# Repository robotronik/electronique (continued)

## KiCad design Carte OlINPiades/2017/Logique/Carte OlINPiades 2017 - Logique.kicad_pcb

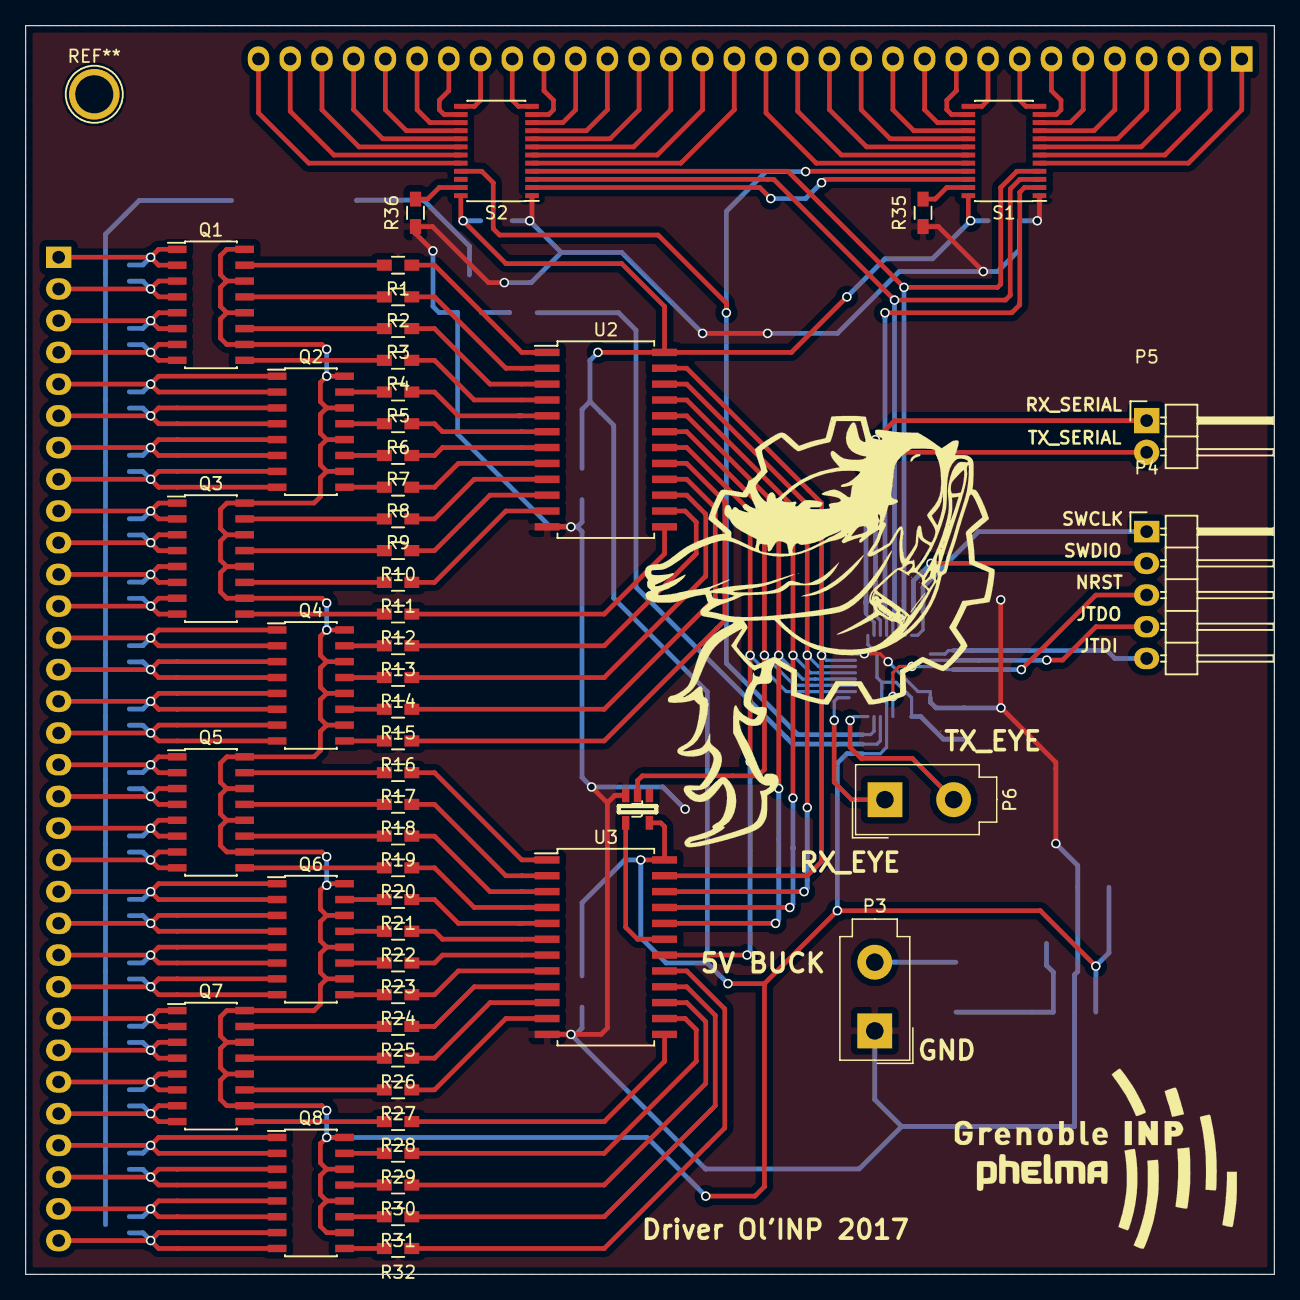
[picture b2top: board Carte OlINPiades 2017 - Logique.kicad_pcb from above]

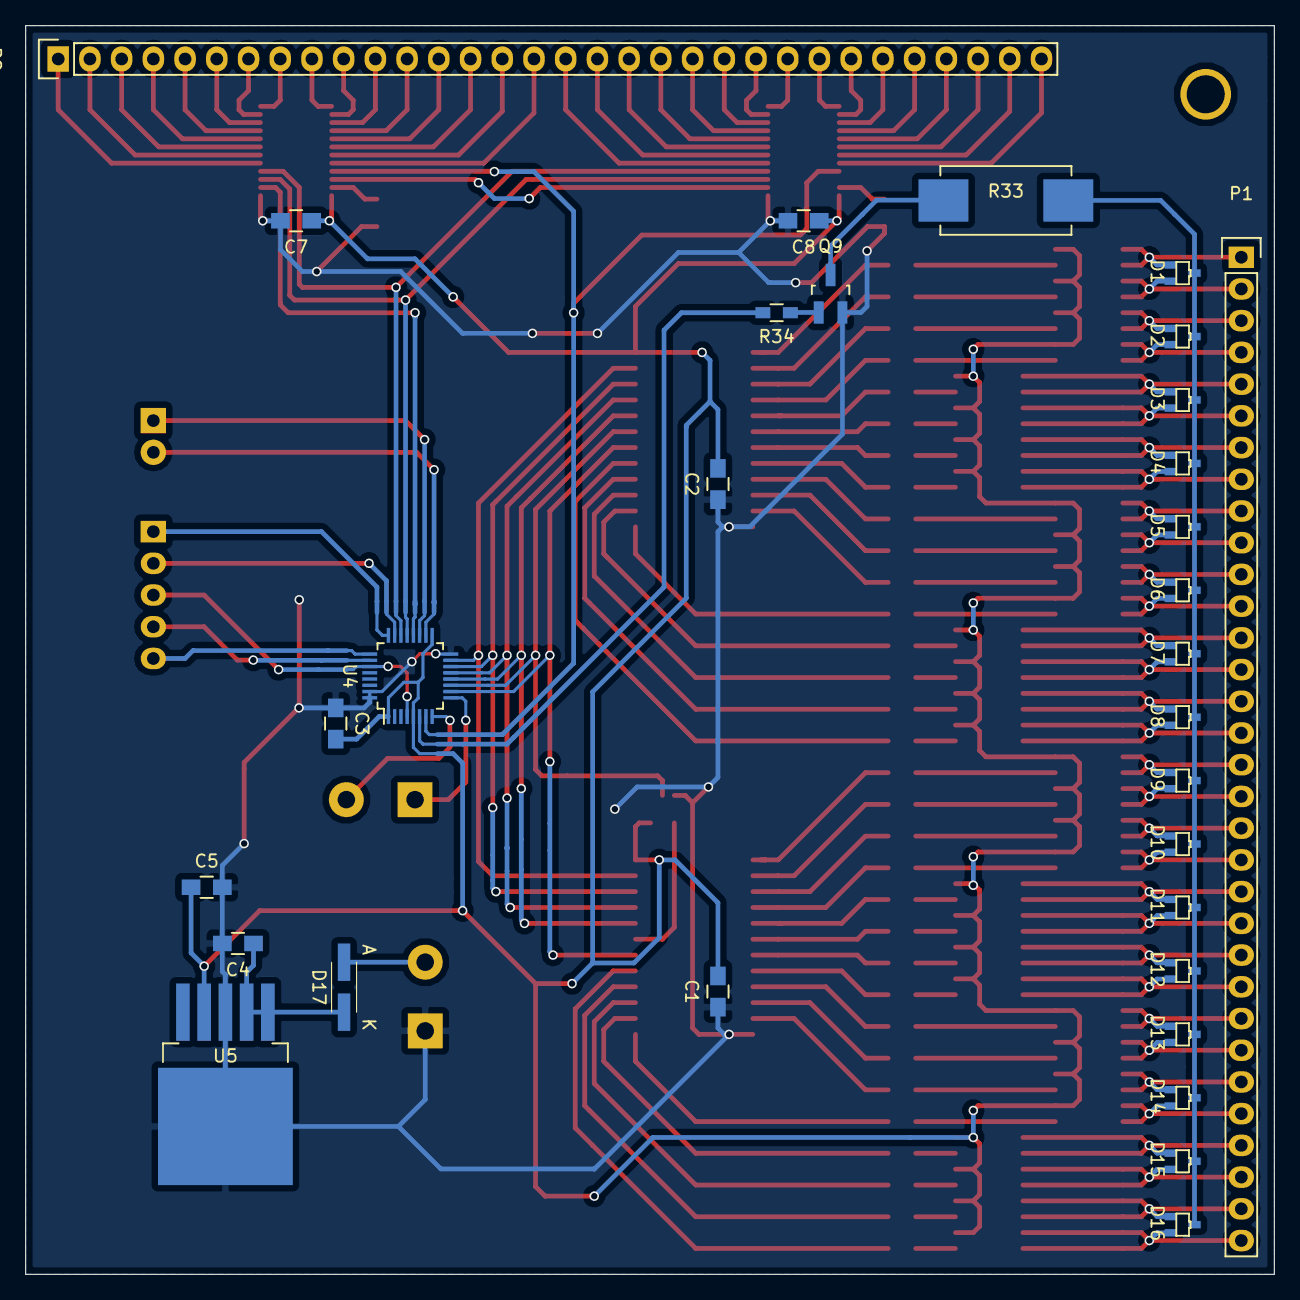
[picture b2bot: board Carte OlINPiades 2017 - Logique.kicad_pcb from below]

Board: 2 copper layers, 100.0 x 100.0 mm, 82 parts (31 on the bottom side), 159 nets.

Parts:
C1, C2: 100n; C_0805_HandSoldering
C3, C7, C8: 100nF; C_0805_HandSoldering
C4: 1µF; C_0805_HandSoldering
C5: 47µF; C_0805_HandSoldering
D1, D2, D3, D4, D5, D6, D7, D8, D9, D10, D11, D12, D13, D14, D15, D16: BAT54CW; SOT-323
D17: RFN2L4STE25; SMA_Handsoldering
P1, P2: CONN_01X32; Pin_Header_Straight_1x32
P3, P6: CONN_01X02; Molex_MiniFit-JR-5556-02A_2x01x4.20mm_Straight
P4: CONN_01X05; Pin_Header_Angled_1x05
P5: CONN_01X02; Pin_Header_Angled_1x02
Q1, Q2, Q3, Q4, Q5, Q6, Q7, Q8: MMPQ2907A; SOIC-16_3.9x9.9mm_Pitch1.27mm
Q9: DSS4160T; SOT-23_Handsoldering
R1, R2, R3, R4, R5, R6, R7, R8, R9, R10, R11, R12, R13, R14, R15, R16, R17, R18, R19, R20, R21, R22, R23, R24, R25, R26, R27, R28, R29, R30, R31, R32: 470; R_0603_HandSoldering
R33: 8.2; SM_3
R34: 1.7k; R_0603_HandSoldering
R35, R36: 4k; R_0603_HandSoldering
S1, S2: CAT4016; TSSOP-24_4.4x7.8mm_Pitch0.65mm
U1: 74AHC1G; SOT-23-5
U2, U3: CD74HC154; SOIC-24_7.5x15.4mm_Pitch1.27mm
U4: STM32F303K8; LQFP-32_5x5mm_Pitch0.5mm
U5: NCP59301DSS33R4G; TO-263-5Lead

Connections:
+3V3: C1.2, C2.2, C3.2, C5.1, C7.1, C8.1, Q1.10, Q1.12, Q1.14, Q1.16, Q2.10, Q2.12, Q2.14, Q2.16, Q3.10, Q3.12, Q3.14, Q3.16, Q4.10, Q4.12, Q4.14, Q4.16, Q5.10, Q5.12, Q5.14, Q5.16, Q6.10, Q6.12, Q6.14, Q6.16, Q7.10, Q7.12, Q7.14, Q7.16, Q8.10, Q8.12, Q8.14, Q8.16, S1.24, S2.24, U1.5, U2.24, U3.24, U4.1, U4.5, U4.17, U5.4
+5V: C4.1, D17.1, U5.1, U5.2
BLANK: S1.21, S2.21, U4.7
CLK_COL: S1.3, S2.3, U4.21
DATA: U2.18, U3.18, U4.10
GND: C1.1, C2.1, C3.1, C4.2, C5.2, C7.2, C8.2, P3.1, Q9.2, R35.1, R36.1, S1.1, S2.1, U1.3, U2.12, U3.12, U4.16, U4.31, U4.32, U5.3
JTDI: P4.5, U4.25
JTDO: P4.4, U4.26
LATCH_COL: S1.4, S2.4, U4.22
LINE_0: U2.23, U3.23, U4.15
LINE_1: U2.22, U3.22, U4.14
LINE_2: U2.21, U3.21, U4.13
LINE_3: U2.20, U3.20, U4.12
LINE_4: U1.2, U2.19, U4.11
NRST: P4.3, U4.4, U4.27
unnamed: D1.1, P1.1, Q1.1, Q1.2
unnamed: D1.2, P1.2, Q1.3, Q1.4
unnamed: D1.3, D2.3, D3.3, D4.3, D5.3, D6.3, D7.3, D8.3, D9.3, D10.3, D11.3, D12.3, D13.3, D14.3, D15.3, D16.3, R33.1
unnamed: D2.1, P1.3, Q1.5, Q1.6
unnamed: D2.2, P1.4, Q1.7, Q1.8
unnamed: D3.1, P1.5, Q2.1, Q2.2
unnamed: D3.2, P1.6, Q2.3, Q2.4
unnamed: D4.1, P1.7, Q2.5, Q2.6
unnamed: D4.2, P1.8, Q2.7, Q2.8
unnamed: D5.1, P1.9, Q3.1, Q3.2
unnamed: D5.2, P1.10, Q3.3, Q3.4
unnamed: D6.1, P1.11, Q3.5, Q3.6
unnamed: D6.2, P1.12, Q3.7, Q3.8
unnamed: D7.1, P1.13, Q4.1, Q4.2
unnamed: D7.2, P1.14, Q4.3, Q4.4
unnamed: D8.1, P1.15, Q4.5, Q4.6
unnamed: D8.2, P1.16, Q4.7, Q4.8
unnamed: D9.1, P1.17, Q5.1, Q5.2
unnamed: D9.2, P1.18, Q5.3, Q5.4
unnamed: D10.1, P1.19, Q5.5, Q5.6
unnamed: D10.2, P1.20, Q5.7, Q5.8
unnamed: D11.1, P1.21, Q6.1, Q6.2
unnamed: D11.2, P1.22, Q6.3, Q6.4
unnamed: D12.1, P1.23, Q6.5, Q6.6
unnamed: D12.2, P1.24, Q6.7, Q6.8
unnamed: D13.1, P1.25, Q7.1, Q7.2
unnamed: D13.2, P1.26, Q7.3, Q7.4
unnamed: D14.1, P1.27, Q7.5, Q7.6
unnamed: D14.2, P1.28, Q7.7, Q7.8
unnamed: D15.1, P1.29, Q8.1, Q8.2
unnamed: D15.2, P1.30, Q8.3, Q8.4
unnamed: D16.1, P1.31, Q8.5, Q8.6
unnamed: D16.2, P1.32, Q8.7, Q8.8
unnamed: D17.2, P3.2
unnamed: P2.1, S1.5
unnamed: P2.2, S1.6
unnamed: P2.3, S1.7
unnamed: P2.4, S1.8
unnamed: P2.5, S1.9
unnamed: P2.6, S1.10
unnamed: P2.7, S1.11
unnamed: P2.8, S1.12
unnamed: P2.9, S1.13
unnamed: P2.10, S1.14
unnamed: P2.11, S1.15
unnamed: P2.12, S1.16
unnamed: P2.13, S1.17
unnamed: P2.14, S1.18
unnamed: P2.15, S1.19
unnamed: P2.16, S1.20
unnamed: P2.17, S2.5
unnamed: P2.18, S2.6
unnamed: P2.19, S2.7
unnamed: P2.20, S2.8
unnamed: P2.21, S2.9
unnamed: P2.22, S2.10
unnamed: P2.23, S2.11
unnamed: P2.24, S2.12
unnamed: P2.25, S2.13
unnamed: P2.26, S2.14
unnamed: P2.27, S2.15
unnamed: P2.28, S2.16
unnamed: P2.29, S2.17
unnamed: P2.30, S2.18
unnamed: P2.31, S2.19
unnamed: P2.32, S2.20
unnamed: Q1.9, R4.2
unnamed: Q1.11, R3.2
unnamed: Q1.13, R2.2
unnamed: Q1.15, R1.2
unnamed: Q2.9, R8.2
unnamed: Q2.11, R7.2
unnamed: Q2.13, R6.2
unnamed: Q2.15, R5.2
unnamed: Q3.9, R12.2
unnamed: Q3.11, R11.2
unnamed: Q3.13, R10.2
unnamed: Q3.15, R9.2
unnamed: Q4.9, R16.2
unnamed: Q4.11, R15.2
unnamed: Q4.13, R14.2
unnamed: Q4.15, R13.2
unnamed: Q5.9, R20.2
unnamed: Q5.11, R19.2
unnamed: Q5.13, R18.2
unnamed: Q5.15, R17.2
unnamed: Q6.9, R24.2
unnamed: Q6.11, R23.2
unnamed: Q6.13, R22.2
unnamed: Q6.15, R21.2
unnamed: Q7.9, R28.2
unnamed: Q7.11, R27.2
unnamed: Q7.13, R26.2
unnamed: Q7.15, R25.2
unnamed: Q8.9, R32.2
unnamed: Q8.11, R31.2
unnamed: Q8.13, R30.2
unnamed: Q8.15, R29.2
unnamed: Q9.1, R34.1
unnamed: Q9.3, R33.2
unnamed: R1.1, U2.1
unnamed: R2.1, U2.2
unnamed: R3.1, U2.3
unnamed: R4.1, U2.4
unnamed: R5.1, U2.5
unnamed: R6.1, U2.6
unnamed: R7.1, U2.7
unnamed: R8.1, U2.8
unnamed: R9.1, U2.9
unnamed: R10.1, U2.10
unnamed: R11.1, U2.11
unnamed: R12.1, U2.13
unnamed: R13.1, U2.14
unnamed: R14.1, U2.15
unnamed: R15.1, U2.16
unnamed: R16.1, U2.17
unnamed: R17.1, U3.1
unnamed: R18.1, U3.2
unnamed: R19.1, U3.3
unnamed: R20.1, U3.4
unnamed: R21.1, U3.5
unnamed: R22.1, U3.6
unnamed: R23.1, U3.7
unnamed: R24.1, U3.8
unnamed: R25.1, U3.9
unnamed: R26.1, U3.10
unnamed: R27.1, U3.11
unnamed: R28.1, U3.13
unnamed: R29.1, U3.14
unnamed: R30.1, U3.15
unnamed: R31.1, U3.16
unnamed: R32.1, U3.17
unnamed: R35.2, S1.23
unnamed: R36.2, S2.23
unnamed: S1.22, S2.2
unnamed: U1.4, U3.19
PURGE: R34.2, U4.6
RX_EYE: P6.1, U4.9
RX_SERIAL: P5.1, U4.19
SERIAL_IN: S1.2, U4.20
SWCLK: P4.1, U4.24
SWDIO: P4.2, U4.23
TX_EYE: P6.2, U4.8
TX_SERIAL: P5.2, U4.18

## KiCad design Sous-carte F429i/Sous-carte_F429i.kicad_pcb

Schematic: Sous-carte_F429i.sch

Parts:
D1, D2, D4, D5, D6, D7, D8, D10, D11, D12, D13, D14, D15, D16, D17, D18, D19: LED; LED_0805
D3, D9: D; Diode_DO-35_SOD27_Horizontal_RM10
P1, P2, P4, P5, P6, P7, P8, P12, P15, P16, P17: CONN_01X02; Molex_KK_6410-02
P3, P11: CONN_01X02; bornier2
P9, P13, P14: CONN_01X03; Molex_KK_6410-03
P10, P18, P19, P20, P21, P22, P23, P24, P25, P26, P27, P28, P30, P31, P32, P33, P34, P35, P36, P37, P38, P39, P40, P41, P42, P43, P44, P45, P46, P47, P48, P49, P50, P51, P52, P53, P54, P55, P56, P57, P58, P59, P60, P61, P62, P63, P64, P65, P66, P67, P68, P69, P70, P71, P72, P73, P74, P75, P76, P77, P78, P79, P80, P81, P82, P83, P84, P85, P86, P87, P88, P89, P91, P92, P93, P94, P95, P96, P97, P98, P99, P100, P101, P102, P103, P104, P105, P106, P107, P108, P109, P110, P111, P112, P113, P114, P115, P116, P117: CONN_01X01; Pin_Header_Straight_1x01
R1, R2, R3, R4, R5, R6, R7, R8, R9, R10, R11, R12, R13, R14, R15, R16, R17, R18, R19, R20, R21: R; R_0603_HandSoldering
stm1: STM32F429i-Discovery; stm32f429i-disco

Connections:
+5V: D3.1, D4.2 (A), P4.1, P13.1, P13.2, P13.3, stm1.1, stm1.2
+BATT: D9.1, D10.2 (A), P14.2
EQUIPE: stm1.33; also elsewhere on the board
GND: P3.1, P11.1, P14.1, R1.1, R2.1, R3.1, R4.1, R5.1, R6.1, R7.1, R8.1, R9.2, R10.2, R11.1, R12.2, R13.1, R14.1, R15.1, R16.1, R17.1, R18.2, R19.2, R20.2, R21.2, stm1.63, stm1.64, stm1.75, stm1.93, stm1.127, stm1.128; also elsewhere on the board
LED_1: D16.2 (A), stm1.16
LED_2: D17.2 (A), stm1.13
LED_3: D18.2 (A), stm1.14
LED_4: D19.2 (A), stm1.11
unnamed: D1.1 (K), R1.2
unnamed: D2.1 (K), R2.2
unnamed: D3.2, P3.2
unnamed: D4.1 (K), R6.2
unnamed: D5.1 (K), R3.2
unnamed: D6.1 (K), R4.2
unnamed: D7.1 (K), R7.2
unnamed: D8.1 (K), R8.2
unnamed: D9.2, P11.2
unnamed: D10.1 (K), R13.2
unnamed: D11.1 (K), R11.2
unnamed: D12.1 (K), R14.2
unnamed: D13.1 (K), R15.2
unnamed: D14.1 (K), R16.2
unnamed: D15.1 (K), R17.2
unnamed: D16.1 (K), R18.1
unnamed: D17.1 (K), R19.1
unnamed: D18.1 (K), R20.1
unnamed: D19.1 (K), R21.1
unnamed: P18.1, stm1.3
unnamed: P19.1, stm1.5
unnamed: P20.1, stm1.7
unnamed: P21.1, stm1.9
unnamed: P22.1, stm1.19
unnamed: P23.1, stm1.21
unnamed: P24.1, stm1.23
unnamed: P25.1, stm1.25
unnamed: P26.1, stm1.27
unnamed: P27.1, stm1.29
unnamed: P28.1, stm1.31
unnamed: P30.1, stm1.35
unnamed: P31.1, stm1.39
unnamed: P32.1, stm1.41
unnamed: P33.1, stm1.47
unnamed: P34.1, stm1.49
unnamed: P35.1, stm1.53
unnamed: P36.1, stm1.57
unnamed: P37.1, stm1.59
unnamed: P38.1, stm1.61
unnamed: P39.1, stm1.4
unnamed: P40.1, stm1.6
unnamed: P41.1, stm1.8
unnamed: P42.1, stm1.10
unnamed: P43.1, stm1.12
unnamed: P44.1, stm1.20
unnamed: P45.1, stm1.22
unnamed: P46.1, stm1.24
unnamed: P47.1, stm1.26
unnamed: P48.1, stm1.28
unnamed: P49.1, stm1.30
unnamed: P50.1, stm1.32
unnamed: P51.1, stm1.34
unnamed: P52.1, stm1.36
unnamed: P53.1, stm1.38
unnamed: P54.1, stm1.42
unnamed: P55.1, stm1.46
unnamed: P56.1, stm1.48
unnamed: P57.1, stm1.50
unnamed: P58.1, stm1.54
unnamed: P59.1, stm1.56
unnamed: P60.1, stm1.58
unnamed: P61.1, stm1.60
unnamed: P62.1, stm1.62
unnamed: P63.1, stm1.65, stm1.66
unnamed: P64.1, stm1.69
unnamed: P65.1, stm1.71
unnamed: P66.1, stm1.73
unnamed: P67.1, stm1.77
unnamed: P68.1, stm1.79
unnamed: P69.1, stm1.81
unnamed: P70.1, stm1.83
unnamed: P71.1, stm1.85
unnamed: P72.1, stm1.87
unnamed: P73.1, stm1.89
unnamed: P74.1, stm1.91
unnamed: P75.1, stm1.95
unnamed: P76.1, stm1.97
unnamed: P77.1, stm1.99
unnamed: P78.1, stm1.101
unnamed: P79.1, stm1.103
unnamed: P80.1, stm1.105
unnamed: P81.1, stm1.107
unnamed: P82.1, stm1.109
unnamed: P83.1, stm1.111
unnamed: P84.1, stm1.113
unnamed: P85.1, stm1.115
unnamed: P86.1, stm1.117
unnamed: P87.1, stm1.119
unnamed: P88.1, stm1.121
unnamed: P89.1, stm1.123
unnamed: P91.1, stm1.72
unnamed: P92.1, stm1.74
unnamed: P93.1, stm1.76
unnamed: P94.1, stm1.78
unnamed: P95.1, stm1.80
unnamed: P96.1, stm1.82
unnamed: P97.1, stm1.84
unnamed: P98.1, stm1.86
unnamed: P99.1, stm1.88
unnamed: P100.1, stm1.90
unnamed: P101.1, stm1.92
unnamed: P102.1, stm1.94
unnamed: P103.1, stm1.96
unnamed: P104.1, stm1.98
unnamed: P105.1, stm1.100
unnamed: P106.1, stm1.102
unnamed: P107.1, stm1.104
unnamed: P108.1, stm1.106
unnamed: P109.1, stm1.108
unnamed: P110.1, stm1.110
unnamed: P111.1, stm1.112
unnamed: P112.1, stm1.114
unnamed: P113.1, stm1.116
unnamed: P114.1, stm1.118
unnamed: P115.1, stm1.120
unnamed: P116.1, stm1.122
unnamed: P117.1, stm1.124
START: P4.2, R5.2, stm1.15
SWITCH_0: P9.1, R9.1, stm1.55
SWITCH_1: P9.2, R10.1, stm1.126
SWITCH_2: P9.3, R12.1, stm1.125
UART4_RX: D2.2 (A), P2.2, P6.2, stm1.44
UART4_TX: D6.2 (A), P2.1, P6.1, stm1.45
UART5_RX: D7.2 (A), P7.2, P8.2, stm1.40
UART5_TX: D8.2 (A), P7.1, P8.1, stm1.43
UART7_RX: D12.2 (A), P12.2, P15.2, stm1.67
UART7_TX: D13.2 (A), P12.1, P15.1, stm1.70
UART8_RX: D14.2 (A), P16.2, P17.2, stm1.17
UART8_TX: D15.2 (A), P16.1, P17.1, stm1.18
USART1_RX: D1.2 (A), P1.2, P5.2, stm1.51
USART1_TX: D5.2 (A), P1.1, P5.1, stm1.52
USART2_TX: D11.2 (A), P10.1, P14.3, stm1.37

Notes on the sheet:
UART CAPTEURS US
Devant/Droite
Devant/Gauche
Arrière/Droite
Arrière/Gauche
UART ASSER
UART XL320 Half-Duplex
ALIMENTATIONS
7.5V
DIGITAL INPUTS
Tirette
DIGITAL OUTPUTS
Led debug 1
Led debug 2
Led debug 3
Led debug 4
STM32F429I-DISCOVERY
Configuration coquillages
Equipe

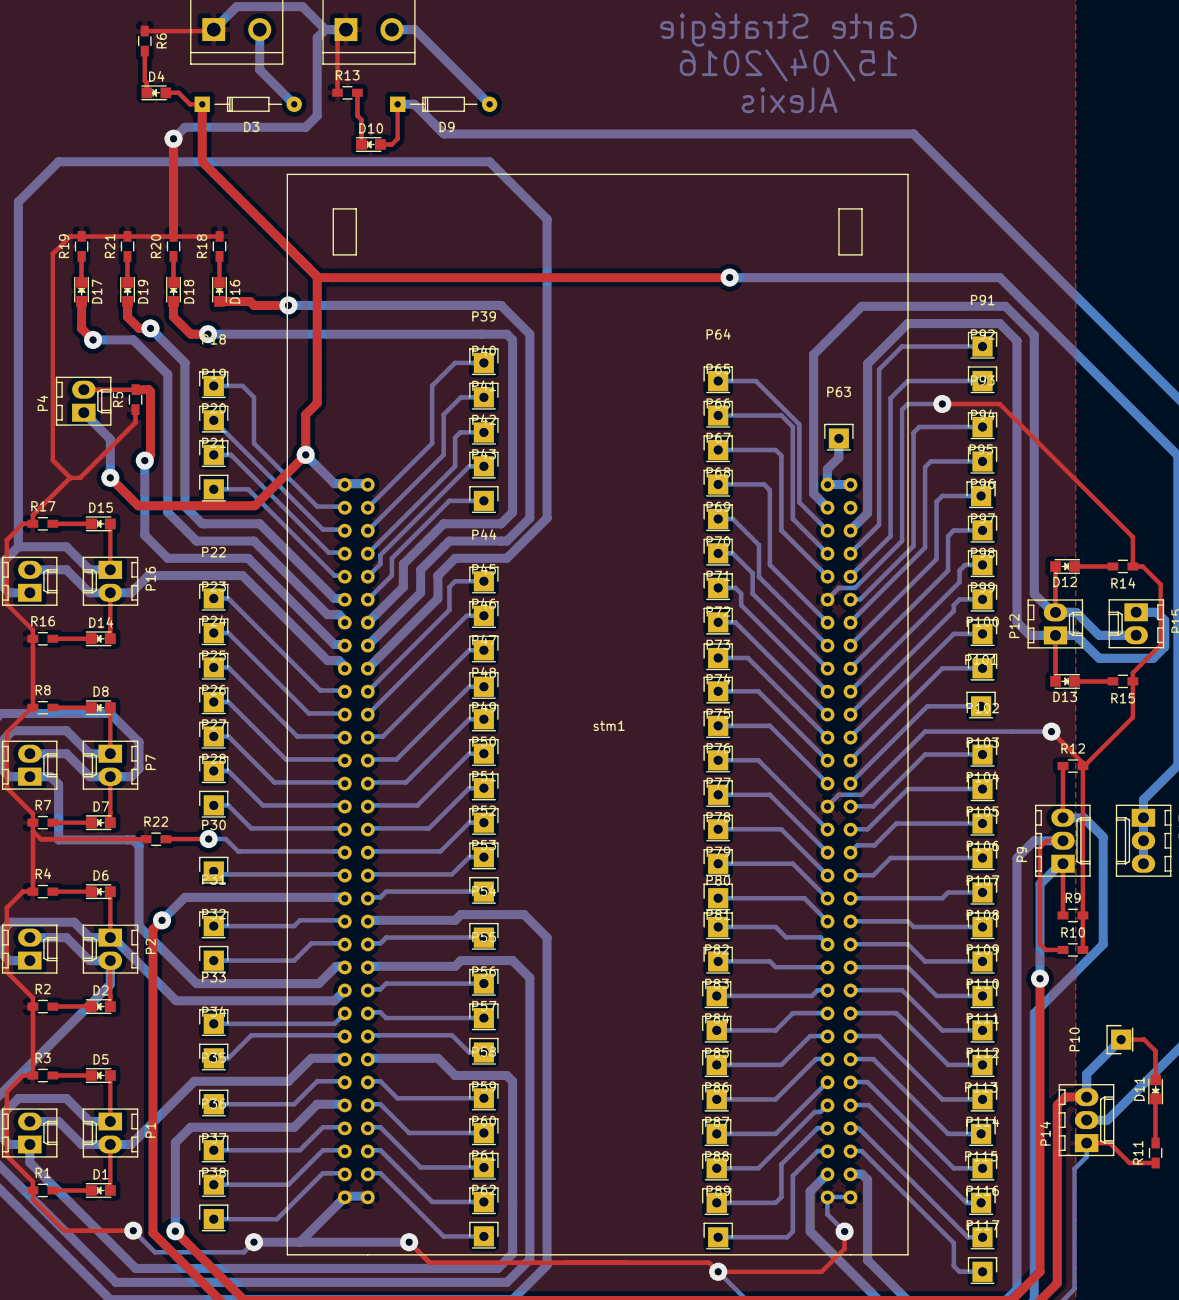
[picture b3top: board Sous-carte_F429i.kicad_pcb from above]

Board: 2 copper layers, 157 parts (0 on the bottom side), 140 nets.

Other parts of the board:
R22: R; R_0603_HandSoldering

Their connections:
EQUIPE: R22.2; also elsewhere on the board
GND: R22.1; also elsewhere on the board

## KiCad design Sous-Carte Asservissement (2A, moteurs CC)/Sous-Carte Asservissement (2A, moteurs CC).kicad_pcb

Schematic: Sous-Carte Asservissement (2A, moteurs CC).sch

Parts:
D1, D2, D3: LED; LED-3MM
D4: D; D3
P1: CONN_01X18; Pin_Header_Angled_1x18
P2, P3: CONN_01X02; bornier2
P4, P5: CONN_01X04; Pin_Header_Angled_1x04
P6, P7, P8, P9, P10, P11, P12, P13, P14, P15, P16, P17, P18, P19, P20, P21, P22, P23, P24, P25, P26, P27, P28, P29, P30, P31, P32, P33, P34, P35, P36, P37, P38, P39, P40, P41, P42, P43, P44, P45, P46, P47, P48, P49, P50, P51, P52, P53, P54, P55, P56, P57, P58, P59, P60, P61, P62, P63, P64, P65, P66, P67, P68, P69, P70, P71, P72, P73, P74, P75, P76, P77, P78, P79, P80, P81: CONN_01X01; Pin_Header_Straight_1x01
R1, R2, R3: 150; Resistor_Horizontal_RM7mm
stm321: STM32F407-Discovery; STM32F407

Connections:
+5V: D1.2 (A), D4.1, P1.3, P1.10, P4.1, P5.1, stm321.53, stm321.54
GND: P1.2, P1.7, P1.12, P1.16, P2.1, P4.3, P5.3, R1.1, R2.2, R3.1, stm321.1, stm321.2, stm321.5, stm321.23, stm321.49, stm321.50, stm321.51, stm321.52, stm321.99, stm321.100
M1I1: P1.5, stm321.67
M1I2: P1.4, stm321.65
M1PWM: P1.6, stm321.27
M2PWM: P1.15, stm321.29
M2_I1: P1.14, stm321.68
M2_I2: P1.13, stm321.66
unnamed: D1.1 (K), R1.2
unnamed: D2.1 (K), R2.1
unnamed: D3.1 (K), R3.2
unnamed: D4.2, P2.2
unnamed: P6.1, stm321.3
unnamed: P7.1, stm321.7
unnamed: P8.1, stm321.9
unnamed: P9.1, stm321.15
unnamed: P10.1, stm321.17
unnamed: P11.1, stm321.19
unnamed: P12.1, stm321.21
unnamed: P13.1, stm321.25
unnamed: P14.1, stm321.13
unnamed: P15.1, stm321.45
unnamed: P16.1, stm321.31
unnamed: P17.1, stm321.33
unnamed: P18.1, stm321.35
unnamed: P19.1, stm321.37
unnamed: P20.1, stm321.39
unnamed: P21.1, stm321.41
unnamed: P22.1, stm321.43
unnamed: P23.1, stm321.47
unnamed: P24.1, stm321.6
unnamed: P25.1, stm321.8
unnamed: P26.1, stm321.10
unnamed 39: stm321.16; also elsewhere on the board
unnamed: P28.1, stm321.18
unnamed: P29.1, stm321.20
unnamed: P30.1, stm321.22
unnamed: P31.1, stm321.24
unnamed: P32.1, stm321.26
unnamed: P33.1, stm321.28
unnamed: P34.1, stm321.30
unnamed: P35.1, stm321.32
unnamed: P36.1, stm321.34
unnamed: P37.1, stm321.36
unnamed: P38.1, stm321.38
unnamed: P39.1, stm321.40
unnamed: P40.1, stm321.42
unnamed: P41.1, stm321.44
unnamed: P42.1, stm321.46
unnamed: P43.1, stm321.48
unnamed: P44.1, stm321.55
unnamed: P45.1, stm321.57
unnamed: P46.1, stm321.59
unnamed: P47.1, stm321.61
unnamed: P48.1, stm321.63
unnamed: P49.1, stm321.69
unnamed: P50.1, stm321.71
unnamed: P51.1, stm321.77
unnamed: P52.1, stm321.79
unnamed: P53.1, stm321.81
unnamed: P54.1, stm321.83
unnamed: P55.1, stm321.85
unnamed: P56.1, stm321.89
unnamed: P57.1, stm321.91
unnamed: P58.1, stm321.93
unnamed: P59.1, stm321.95
unnamed: P60.1, stm321.4
unnamed: P61.1, stm321.56
unnamed: P62.1, stm321.58
unnamed: P63.1, stm321.60
unnamed: P64.1, stm321.62
unnamed: P65.1, stm321.64
unnamed: P66.1, stm321.70
unnamed: P67.1, stm321.74
unnamed: P68.1, stm321.73
unnamed: P69.1, stm321.78
unnamed: P70.1, stm321.80
unnamed: P71.1, stm321.82
unnamed: P72.1, stm321.84
unnamed: P73.1, stm321.86
unnamed: P74.1, stm321.75
unnamed: P75.1, stm321.92
unnamed: P76.1, stm321.94
unnamed: P77.1, stm321.96
unnamed: P78.1, stm321.98
unnamed: P79.1, stm321.72
unnamed: P80.1, stm321.12
unnamed: P81.1, stm321.14
TIM2_CH1: P4.4, stm321.90
TIM2_CH2: P4.2, stm321.11
TIM3_CH1: P5.4, stm321.97
TIM3_CH2: P5.2, stm321.76
UART_RX: D2.2 (A), P3.1, stm321.88
UART_TX: D3.2 (A), P3.2, stm321.87

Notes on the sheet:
Connecteur Driver Moteurs Pololu
Connecteurs Codeurs

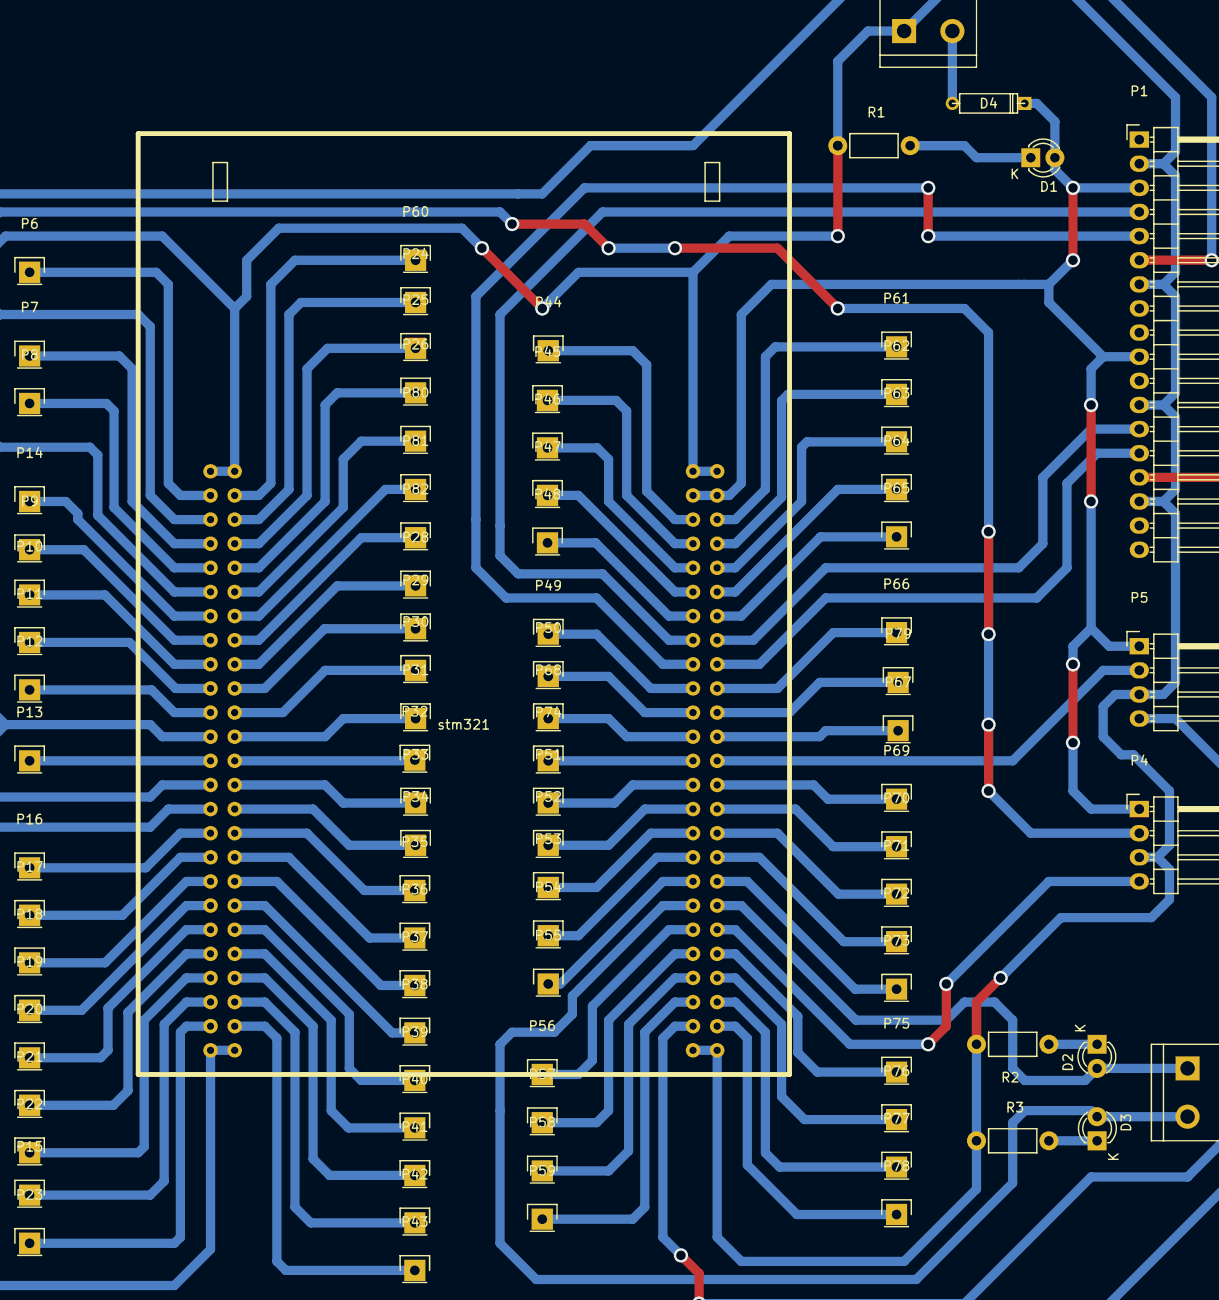
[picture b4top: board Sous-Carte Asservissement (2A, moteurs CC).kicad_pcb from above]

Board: 2 copper layers, 89 parts (0 on the bottom side), 94 nets.

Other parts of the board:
P82: CONN_01X01; Pin_Header_Straight_1x01

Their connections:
unnamed 39: P82.1; also elsewhere on the board

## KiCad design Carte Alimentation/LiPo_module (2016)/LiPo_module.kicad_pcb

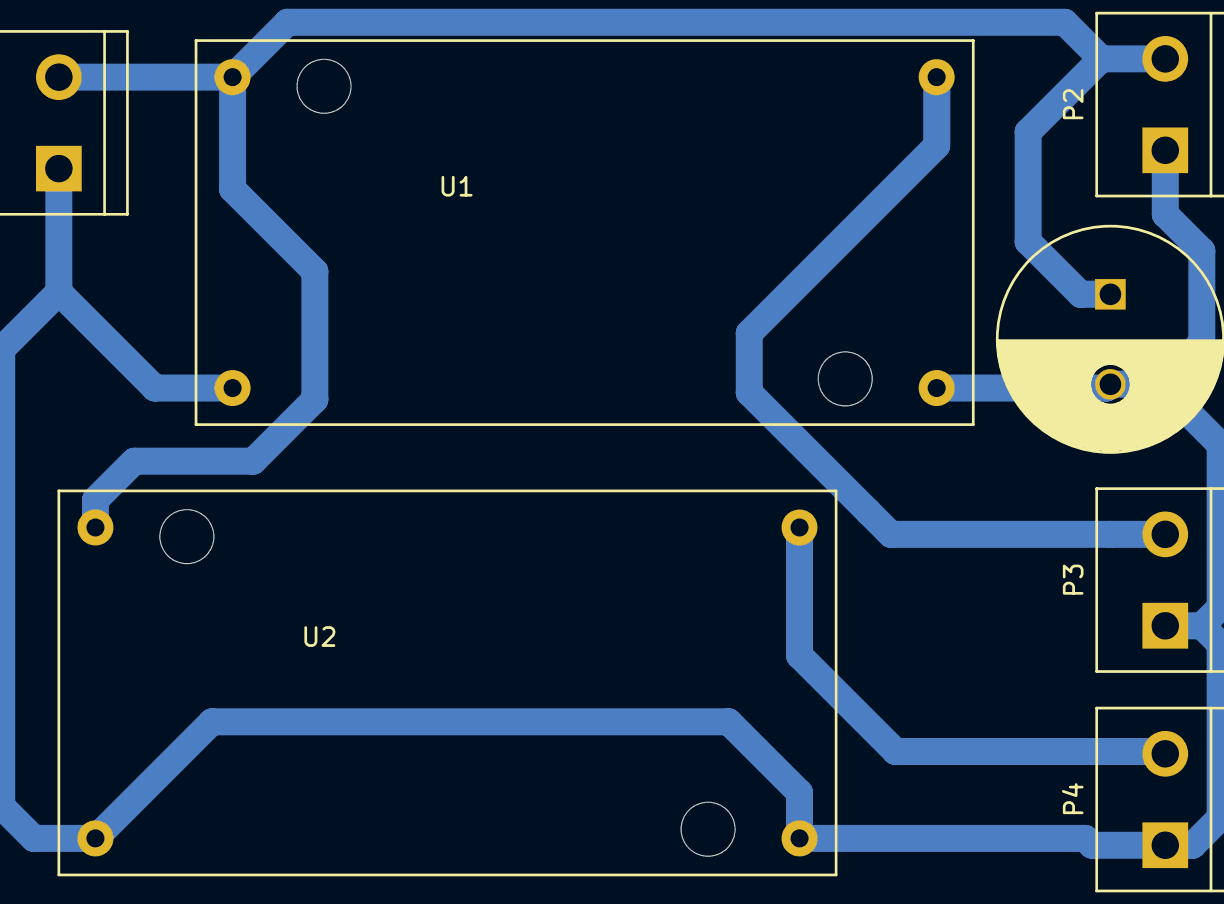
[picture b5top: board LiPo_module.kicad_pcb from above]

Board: 2 copper layers, 7 parts (0 on the bottom side), 4 nets.

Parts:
C1: CP; C_Radial_D12.5_L25_P5
P1, P2, P3, P4: CONN_01X02; bornier2
U1, U2: DSN2596

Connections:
GND: C1.2, P1.1, P2.1, P3.1, P4.1, U1.2, U1.3, U2.2, U2.3
unnamed: C1.1, P1.2, P2.2, U1.1, U2.1
unnamed: P3.2, U1.4
unnamed: P4.2, U2.4

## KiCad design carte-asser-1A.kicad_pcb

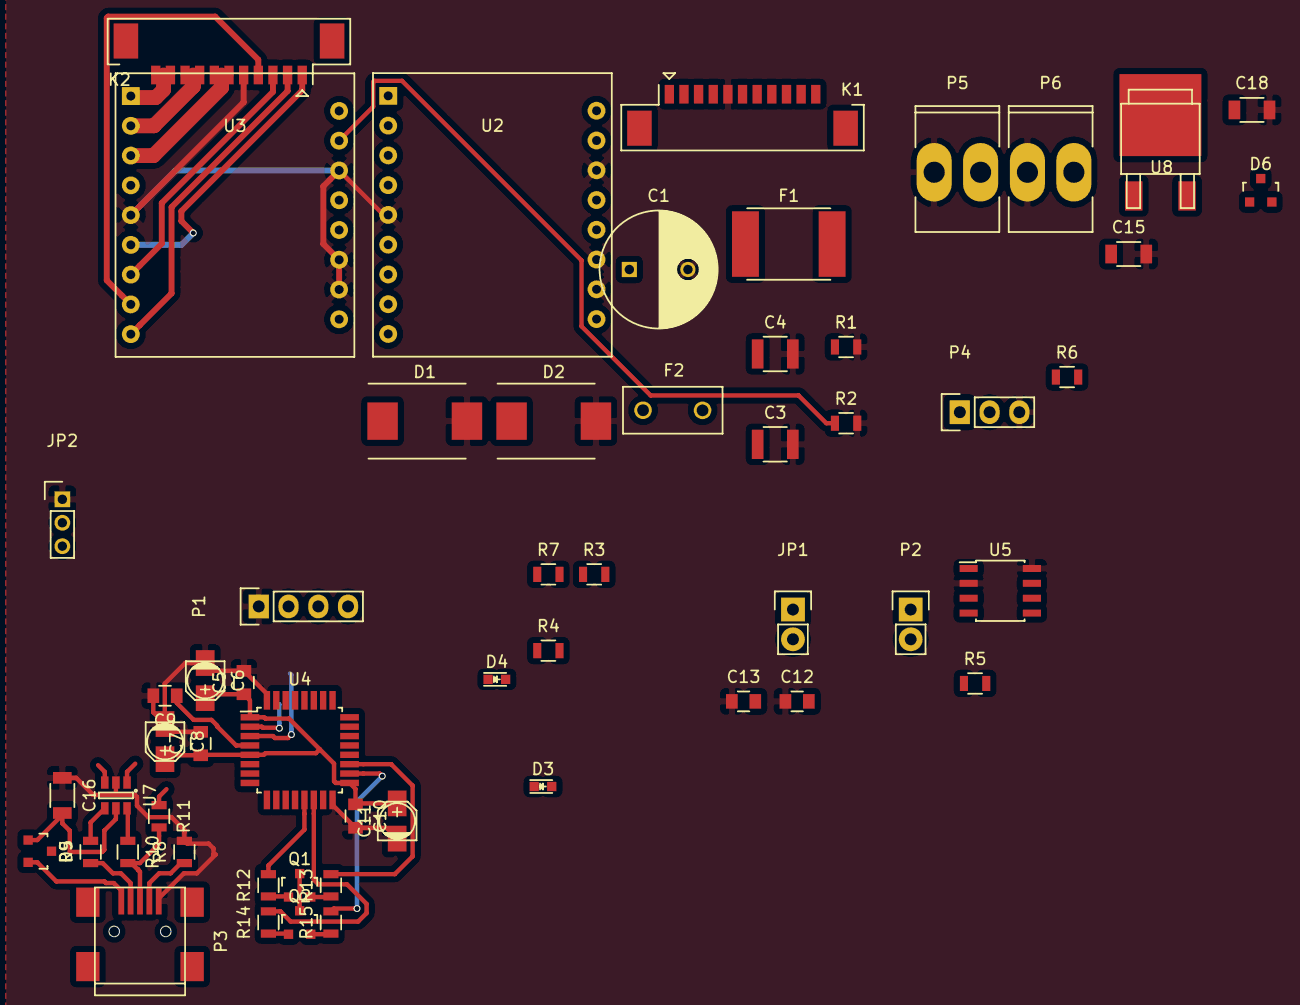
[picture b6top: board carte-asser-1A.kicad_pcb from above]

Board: 2 copper layers, 56 parts (0 on the bottom side), 57 nets.

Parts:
C1: 100u/35v; C_Radial_D10_L13_P5
C3, C4: 45nF/50v; C_1210
C5, C9, C12, C13: 100n; C_0805
C6: 4.7u; c_elec_3x5.3
C7, C10: 10n; C_0805
C8, C11: 1u; c_elec_3x5.3
C15, C18: 330n; C_1206
C16: 100n; C_1206
D1, D2: Schottky/26V; DO-214AB
D3, D4: LED; LED_0603
D5, D6: D_Small; SOT-23
F1: FUSE/3A; Fuse_SMD2920
F2: FUSE/3A; Fuse_TE5_Littlefuse-395Series
JP1: CAN termination; Pin_Header_Straight_1x02
JP2: JUMPER3; Pin_Header_Straight_1x03_Pitch2.00mm
K1, K2: Maxon-200142; Molex_PicoBlade_53261-1171
P1: swdio; Pin_Header_Straight_1x04
P2: CAN bus; Pin_Header_Straight_1x02
P3: USB_OTG; USB_Mini-B
P4: serial bus; Socket_Strip_Straight_1x03
P5: 5V; Socket_MOLEX-KK-RM3-96mm_Lock_2pin_straight
P6: 8..24V; Socket_MOLEX-KK-RM3-96mm_Lock_2pin_straight
Q1, Q2: Q_PNP_BCE; SOT-23
R1, R2, R7, R12, R14: 10k; R_0805
R3: 1K; R_0805
R4, R6: 1k; R_0805
R5: 120; R_0805
R8: 10K; R_0805
R9, R10: 22; R_0805
R11: 1.5k; R_0805
R13, R15: 100; R_0805
U2, U3: DEC24/2; DE24-2
U4: stm32f042k6tx; TQFP-32_7x7mm_Pitch0.8mm
U5: MCP2562; SOIC-8_3.9x4.9mm_Pitch1.27mm
U7: USBLC6-2; SOT-23-6
U8: MC7805CDTG; SOT-428

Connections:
+3V3: C5.1, C6.1, C7.1, C8.1, C10.1, C11.1, C12.2, C18.1, JP2.3, R3.1, R4.1, R11.1, U4.1, U4.5, U4.17, U5.5
+5V: C13.2, C15.1, C16.2, D5.1, D6.1, U5.3, U7.5
+5V_weak: K1.1, Q1.3, Q2.3, U2.6
+24V: C1.1, F1.1, F2.1, P6.2
/brushless-part/motor1_speed: Q1.2, R13.1, U2.17
/brushless-part/motor2_speed: Q2.2, R15.1, U3.17
/serial-part/rx: P4.1, P4.2, R6.1, R6.2, U4.8, U4.9
/uC-part/can_rx: U4.21, U5.4, U7.3
/uC-part/can_tx: U4.22, U5.1, U7.1
/uC-part/gpio_direction1: U2.14, U4.15
/uC-part/gpio_direction2: U3.14, U4.26
/uC-part/gpio_enable: U2.13, U3.13, U4.20
/uC-part/gpio_ready1: U2.10, U4.10
/uC-part/gpio_ready2: U3.10, U4.11
/uC-part/led1: D4.1, U4.29
/uC-part/led2: D3.1, U4.30
/uC-part/nrst: C9.1, P1.2, U4.4
/uC-part/pwm1_neg: R12.2, U4.13
/uC-part/pwm1_pos: R13.2, U4.19
/uC-part/pwm2_neg: R14.2, U4.14
/uC-part/pwm2_pos: R15.2, U4.18
/uC-part/swclk: P1.3, U4.24
/uC-part/swdio: P1.4, U4.23
GND: C1.2, C3.2, C4.2, C5.2, C6.2, C7.2, C8.2, C9.2, C10.2, C11.2, C12.1, C13.1, C15.2, C16.1, C18.2, D1.2, D2.2, JP2.1, K1.5, K2.5, P1.1, P3.5, P4.3, P5.1, P6.1, R1.2, R2.2, R8.2, U2.5, U2.11, U2.12, U2.15, U3.5, U3.11, U3.12, U3.15, U4.16, U4.32, U5.2, U5.8, U7.2
unnamed: C3.1, D1.1, F1.2, U2.4
unnamed: C4.1, D2.1, F2.2, U3.4
unnamed: D3.2, R3.2
unnamed: D4.2, R4.2
unnamed: D5.2, P3.1
unnamed: D6.2, P5.2
unnamed: JP1.1, P2.1, U5.7
unnamed: JP1.2, R5.1
unnamed: JP2.2, R7.1
unnamed: K1.2, U2.9
unnamed: K1.3, U2.7
unnamed: K1.4, U2.8
unnamed: K1.6, K1.7, U2.3
unnamed: K1.8, K1.9, U2.2
unnamed: K1.10, K1.11, U2.1
unnamed: K2.1, U3.6
unnamed: K2.2, U3.9
unnamed: K2.3, U3.7
unnamed: K2.4, U3.8
unnamed: K2.6, K2.7, U3.3
unnamed: K2.8, K2.9, U3.2
unnamed: K2.10, K2.11, U3.1
unnamed: P2.2, R5.2, U5.6
unnamed: P3.2, R9.1
unnamed: P3.3, R10.2, R11.2
unnamed: P3.4, R8.1
unnamed: Q1.1, R12.1
unnamed: Q2.1, R14.1
unnamed: R1.1, U2.16
unnamed: R2.1, U3.16
unnamed: R7.2, U4.31
unnamed: R9.2, U7.4
unnamed: R10.1, U7.6

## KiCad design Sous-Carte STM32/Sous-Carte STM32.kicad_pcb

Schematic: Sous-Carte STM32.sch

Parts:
D1, D2, D3, D4, D5, D6, D7, D8, D9, D10, D11, D12, D13: LED; LED-3MM
J1: RJ45; RJ45_8
P1: CONN_01X04; Pin_Header_Straight_1x04
P3, P5, P6: CONN_01X02; bornier2
P7: CONN_02X25; Pin_Header_Straight_2x25
R1, R2, R3, R4, R5, R6, R7, R8, R9, R10, R11, R12, R13: R; R4
stm321: STM32F407-Discovery; STM32F407

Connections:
+3V3: stm321.55, stm321.56
+5V: D13.1 (K), P1.2, P5.1, stm321.53, stm321.54
A0: P7.11, stm321.12
A1: P7.9, stm321.11
A2: P7.15, stm321.14
A3: P7.13, stm321.13
B1: P7.21, stm321.21
B3: P7.43, stm321.78
B4: P7.39, stm321.75
B5: P7.41, stm321.76
B6: P7.35, stm321.73
B7: P7.37, stm321.74
B8: P7.31, stm321.69
B9: P7.33, stm321.70
B10: P7.27, stm321.34
B11: P7.29, stm321.35
B12: D1.1 (K), stm321.36
B13: D2.1 (K), stm321.37
B14: D3.1 (K), stm321.38
B15: D4.1 (K), stm321.39
C1: P7.3, stm321.7
C2: P7.7, stm321.10
C3: P7.5, stm321.9
C4: P7.19, stm321.20
C5: P7.17, stm321.19
C8: P7.45, stm321.95
C9: P7.47, stm321.96
E4: P7.14, stm321.63
E5: P7.16, stm321.64
E6: P7.18, stm321.61
E7: P7.20, stm321.25
E8: P7.22, stm321.26
E9: P7.24, stm321.27
E10: P7.26, stm321.28
E11: P7.28, stm321.29
E12: P7.30, stm321.30
E13: P7.32, stm321.31
E14: P7.34, stm321.32
E15: P7.36, stm321.33
GND: P1.1, P5.2, P7.1, P7.2, P7.4, P7.6, P7.8, P7.10, P7.12, P7.23, P7.25, P7.38, P7.40, P7.42, P7.44, P7.46, P7.48, P7.49, P7.50, R1.2, R2.2, R3.2, R4.2, R5.2, R6.2, R7.2, R8.2, R9.2, R10.2, R11.2, R12.2, R13.1, stm321.1, stm321.2, stm321.5, stm321.23, stm321.49, stm321.50, stm321.51, stm321.52, stm321.99, stm321.100
unnamed: D1.2 (A), R1.1
unnamed: D2.2 (A), R2.1
unnamed: D3.2 (A), R3.1
unnamed: D4.2 (A), R4.1
unnamed: D5.2 (A), R5.1
unnamed: D6.2 (A), R6.1
unnamed: D7.2 (A), R7.1
unnamed: D8.2 (A), R8.1
unnamed: D9.2 (A), R9.1
unnamed: D10.2 (A), R10.1
unnamed: D11.2 (A), R11.1
unnamed: D12.2 (A), R12.1
unnamed: D13.2 (A), R13.2
UART2_RX: D6.1 (K), P3.1, stm321.80
UART2_TX: D5.1 (K), P3.2, stm321.79
UART3_RX: D8.1 (K), J1.3, stm321.41
UART3_TX: D7.1 (K), J1.2, stm321.40
UART4_RX: D10.1 (K), P1.3, stm321.88
UART4_TX: D9.1 (K), P1.4, stm321.87
UART5_RX: D12.1 (K), P6.1, stm321.84
UART5_TX: D11.1 (K), P6.2, stm321.85

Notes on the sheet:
STM32F4-Discovery
Inverser les deux si convention contraire sur les autres cartes
Connecteur Asser
ADC
PWM
Digital I/O
vérifier si c'est bien ces connecteurs sur la carte asser
Bornier alim
TIM2_CH4
TIM10_CH1/TIM4_CH3
TIM4_CH2
TIM3_CH1
TIM3_CH2
TIM2_CH2
TIM8_CH3/TIM3_CH3
TIM8_CH4/TIM3_CH4
TIM11_CH1/TIM4_CH4
TIM4_CH1
TIM2_CH3
LED débug
LED UART
